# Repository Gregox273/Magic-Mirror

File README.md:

# Magic-Mirror
iCAN Magic Mirror Project

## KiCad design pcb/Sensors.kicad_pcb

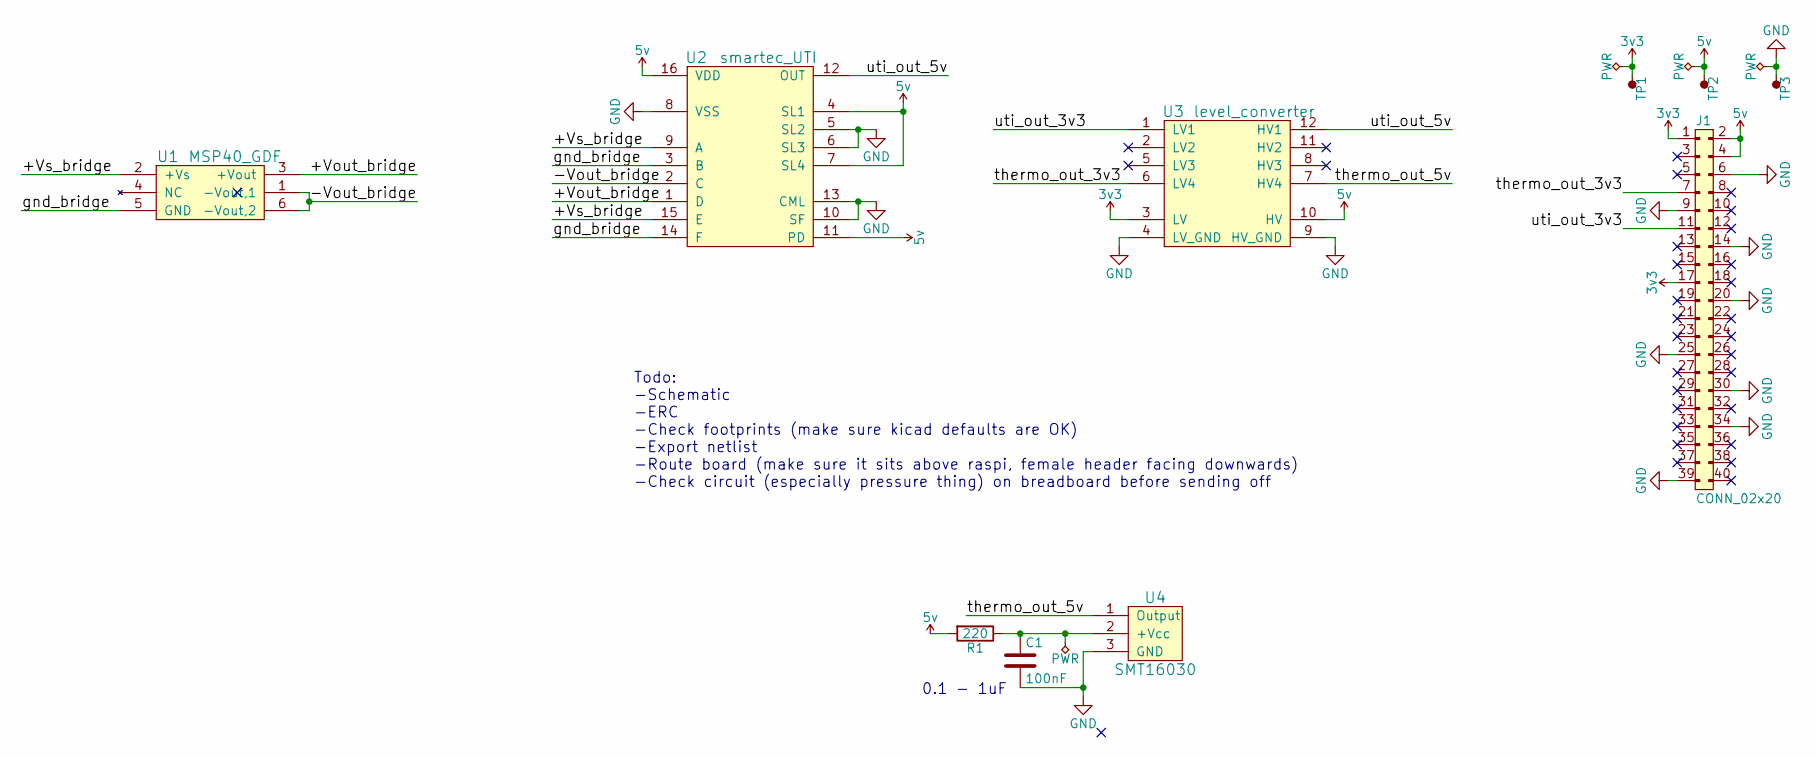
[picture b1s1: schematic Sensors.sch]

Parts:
C1: 100nF; rectangular_capacitor_5mm_pitch; Farnell Value
J1: CONN_02x20; DIL-254P-40; Farnell Value
R1: 220; Resistor_Horizontal_RM15mm; Farnell Value
TP1, TP2, TP3: TESTPAD; TESTPAD_3mm; Farnell Value
U1: MSP40_GDF; Farnell Value
U2: smartec_UTI; DIP-16_W7.62mm_LongPads; Farnell Value
U3: level_converter; Level_converter; Farnell Value
U4: SMT16030; TO-92_Molded_Wide; Farnell Value

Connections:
3v3: J1.1, J1.17, TP1.1, U3.3 (LV)
5v: J1.2, J1.4, R1.2, TP2.1, U2.4 (SL1), U2.7 (SL4), U2.11 (PD), U2.16 (VDD), U3.10 (HV)
/+Vout_bridge: U1.3 (+Vout), U2.1 (D)
/+Vs_bridge: U1.2 (+Vs), U2.9 (A), U2.15 (E)
/-Vout_bridge: U1.1 (-Vout,1), U1.6 (-Vout,2), U2.2 (C)
/gnd_bridge: U1.5 (GND), U2.3 (B), U2.14 (F)
/thermo_out_3v3: J1.7, U3.6 (LV4)
/thermo_out_5v: U3.7 (HV4), U4.1 (Output)
/uti_out_3v3: J1.11, U3.1 (LV1)
/uti_out_5v: U2.12 (OUT), U3.12 (HV1)
GND: C1.2, J1.6, J1.9, J1.14, J1.20, J1.25, J1.30, J1.34, J1.39, TP3.1, U2.5 (SL2), U2.6 (SL3), U2.8 (VSS), U2.10 (SF), U2.13 (CML), U3.4 (LV_GND), U3.9 (HV_GND), U4.3 (GND)
unnamed: C1.1, R1.1, U4.2 (+Vcc)

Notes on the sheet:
Todo: -Schematic -ERC -Check footprints (make sure kicad defaults are OK) -Export netlist -Route board (make sure it sits above raspi, female header facing downwards) -Check circuit (especially pressure thing) on breadboard before sending off
0.1 - 1uF

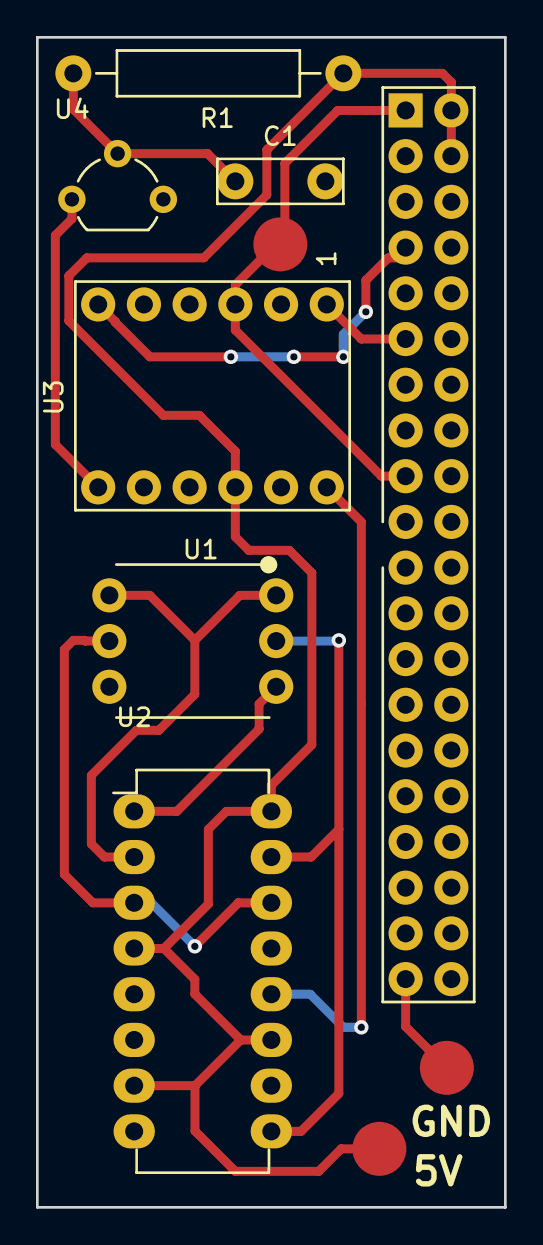
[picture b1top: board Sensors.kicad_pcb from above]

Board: 2 copper layers, 26.0 x 65.0 mm, 10 parts (0 on the bottom side), 12 nets.

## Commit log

2016-03-16 Create index.php
    Top level php script
2016-03-26 Add components to schematic, begin schematic
2016-03-28 Add URLs for two methods of pwm reading on the rpi
2016-03-30 Add to schematic and footprints
2016-04-08 Route PCB
2016-04-22 Add jpegs
